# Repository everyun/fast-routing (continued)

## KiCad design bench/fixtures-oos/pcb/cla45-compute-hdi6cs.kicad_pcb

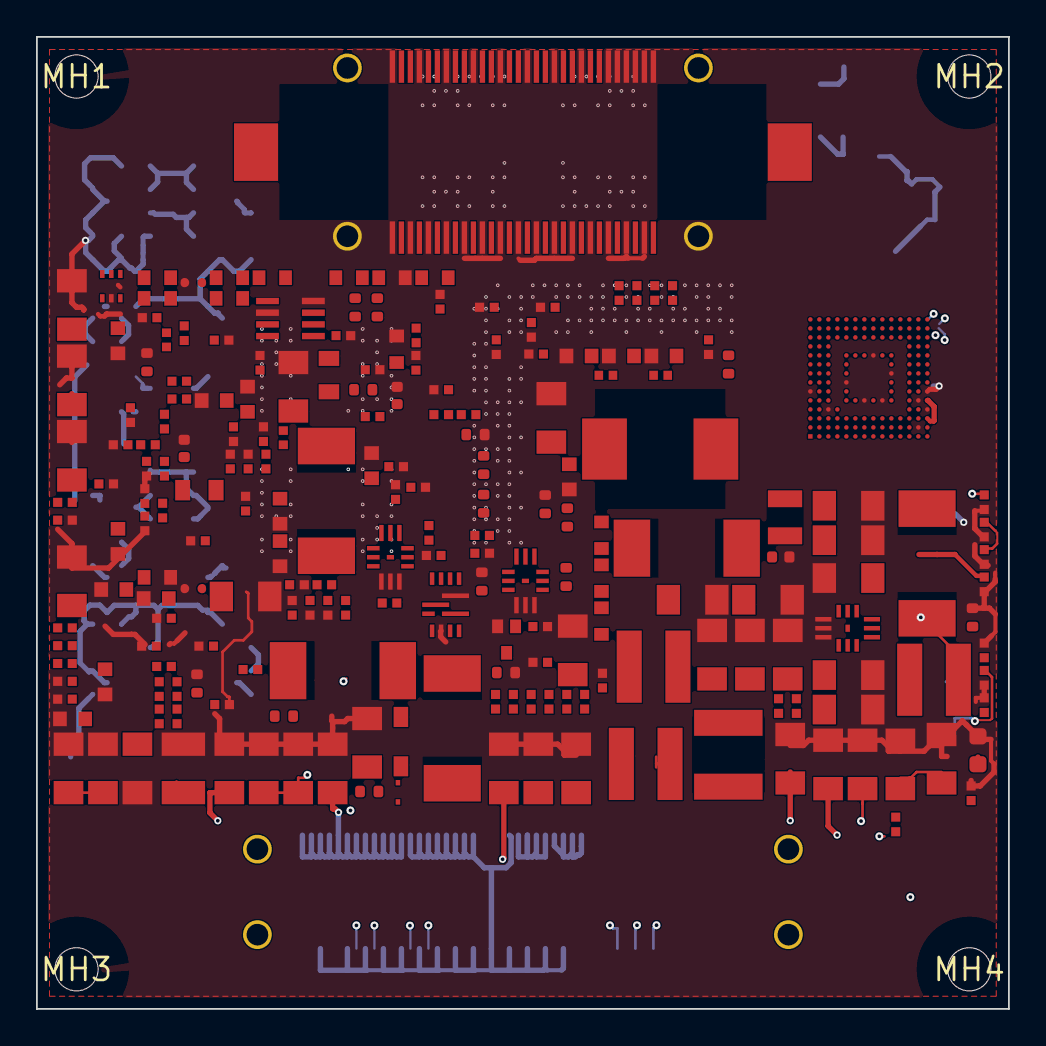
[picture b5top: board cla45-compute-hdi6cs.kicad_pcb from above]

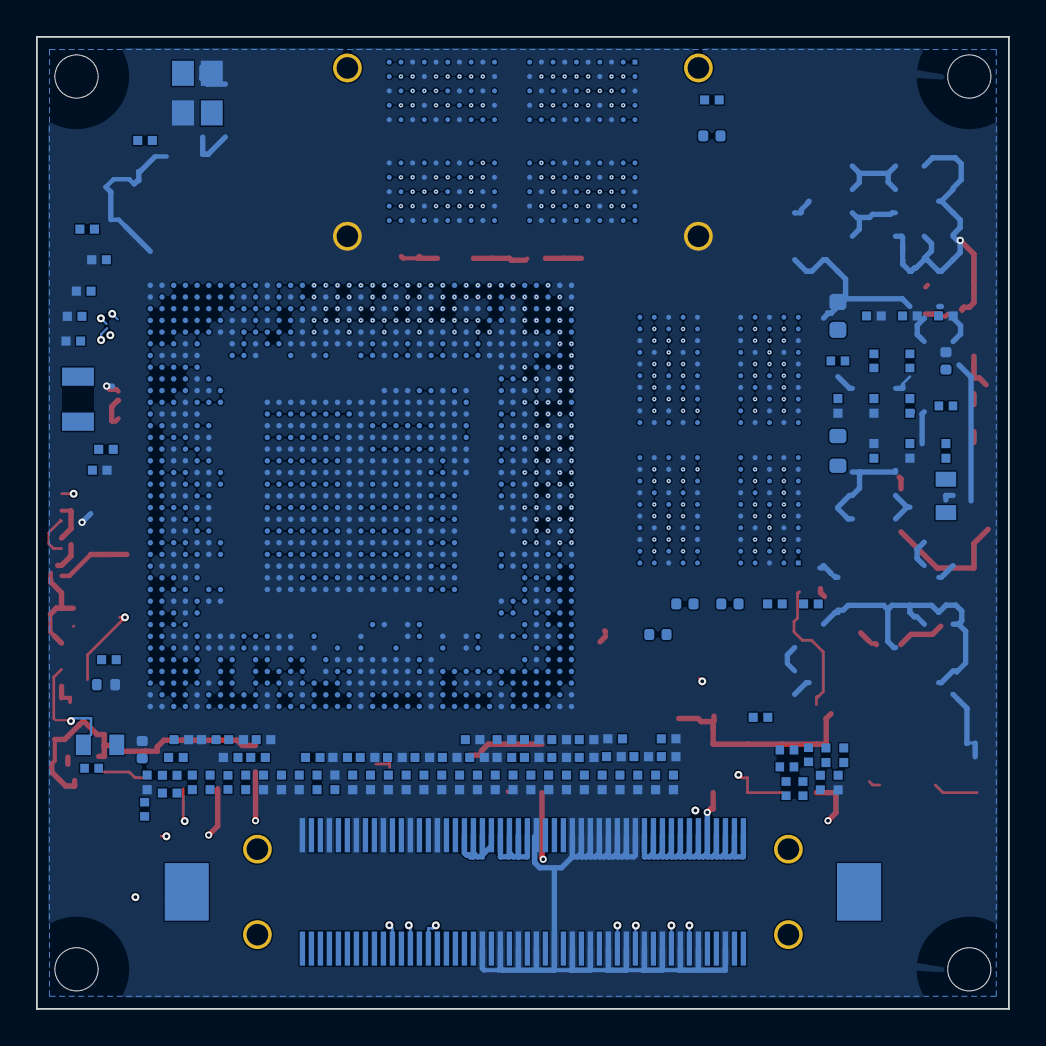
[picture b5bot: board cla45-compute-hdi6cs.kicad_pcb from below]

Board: 6 copper layers, 54.0 x 54.0 mm, 324 parts (113 on the bottom side), 363 nets.

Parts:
C4, C94, C106, C108, C113, C117, C122, C123, C176, C229, C332: SMD Ceramic Capacitor,16V,100nF,+/-10%,X7R,0402,BT
C8, C245, C319, C320, C321, C322, C323: 220nF
C9, C15, C22, C155, C156, C157, C159, C238: Chip Multilayer Ceramic Capacitor,6.3V,100uF,+/-2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
C28, C87, C88, C89, C90, C298: SMD Ceramic Capacitor,6.3V,2200nF,+/-10%,X7S,0402
C36, C99, C104, C105, C107, C116, C124, C142, C144, C145, C151, C239, C241, C247, C264, C267, C360, C425, C437, C438, C449, C451, C457, C461, C468, C478, C479, C530, C531: 100nF
C63, C400, C510, C513, C515, C517, C519, C522, C548, C550, C552, C554, C570: 10uF
C136, C545: 22pF
C137: 100pF
C140, C206, C258, C259, C260, C261, C276, C417, C418, C419, C420, C421, C422, C424, C426, C428, C429, C430, C431, C482: DMBLITE_08071747_SMD Ceramic Capacitor,10V,1000nF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
C143, C243, C257, C324, C384, C386, C387, C388, C389, C390, C391, C392, C393, C398, C403: 1uF
C149: DMBLITE_08072081_SMD Ceramic Capacitor,6.3V,4700n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
C161: DMBLITE_08070862_SMD Ceramic Capacitor,6.3V,22000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
C175, C177, C179, C180, C188, C189, C191, C192, C454, C455, C456: 22uF
C178, C181, C182, C190, C250, C252, C460: SMD Ceramic Capacitor,10V,22000nF,+/-10%,X7S,1206
C195: DMBLITE_08071624_SMD Ceramic Capacitor,6.3V,10000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
C202, C231: DMBLITE_08071990_SMD Ceramic Capacitor,6.3V,2200n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
C230, C244: SMD Ceramic Capacitor,6.3V,47000nF,+/-20%,X5R,1206
C234, C235, C499, C500: 100uF
C246: Chip Multilayer Ceramic Capacitor,50V,220pF+/-10%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
C248: Chip Multilayer Ceramic Capacitor,50V,0.1uF+/-10%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
C251: 22uF 25V X7R +/-10% 1210
C283, C329, C459, C462: DMBLITE_08070449_SMD Ceramic Capacitor,16V,10nF,+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
C325, C326, C328: 4.7uF
C334, C335: 22pF 50V C0G +/-5%
C447, C452: 18pF 50V C0G +/-5%
C800, C801, C802, C803: 1pF 25V C0G 0402 DDR CK differential shunt; C_0402_1005Metric
C810: 1uF 10V X5R 0402; C_0402_1005Metric
C811, C814: 2.2uF 10V X5R 0603; C_0603_1608Metric
C812, C813, C815, C816: 100nF 50V X7R 0402; C_0402_1005Metric
D4: DMBLITE_HBVTA002_NSR0230P2_CURRENT_MPN_LAND_HOLD
D36: DMBLITE_15010252_Silicon schottky diode,Vr=10V,If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
J_CAM: FX23L-60S-0.5SV-SEL
J_CORE: FX23L-100P-0.5SV12-SEL
L2, L6, L11: 1uH
L7: 0.4uH
L10, L12: 2.2uH
LB2, LB8, LB33, LB34, LB40, LB41, LB43, LB51, LB54, LB55: DMBLITE_10070019_EMI beads,+/-25%,1000ohm,1.25ohm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
LB21, LB50, LB53, LB56: DMBLITE_10070013_EMI beads,+/-25%,600ohm,0.65ohm,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
LB42: DMBLITE_10100616_Terminal EMI Bead,120ohm,+/-25%,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
LB52: 1000ohm@100MHz
MH1, MH2, MH3, MH4: NPTH_M2_CLEARANCE_D2.4_KEEP_OUT_D6.0
Q1: NPN 40V 600mA SOT-416/SC-75
R1, R29, R41, R43: Chip Thick Film Resistor,1/10W,27kohm,+/-1%,0603-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
R3: 3.3ohm
R4: Chip Thick Film Resistor,1/10W,12.7kohm,+/-1%,060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
R16, R42, R254, R264: 240ohm
R28, R36: 2kohm
R32: Chip Thick Film Resistor,1/16W,47kohm,+/-1%,0402
R39, R334, R339: 4.7kohm
R47: 100ohm +/-1%
R49, R50, R51: 47kohm
R60, R61, R62: 12.7kohm
R64, R71, R72, R73: 5mohm
R77: Chip Thick Film Resistor,1/16W,30kohm+/-1%,0402-P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
R78, R89: Chip Thick Film Resistor,0.0625W,10000ohm,+/-1%,0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
R79: 20kohm
R80, R246, R247, R255, R256, R424: Chip Thick Film Resistor,1/16W,1kohm-+/-1%-0402,BT
R81, R268: DMBLITE_NOT_LISTED_DNP_INTENT_AND_VALUE_HOLD
R86, R92, R118, R437: 10kohm
R87: Chip Thick Film Resistor,1/16W,12kohm,+/-1%,0402
R145: 1Mohm +/-1%
R151, R188, R189, R196, R206, R276, R297: 4.7kohm +/-1%
R153, R274, R275: Chip Thick Film Resistor,1/10W,33.2kohm+/-1%,0603
R154, R228, R250, R279, R281, R399: 0ohm
R155: DMBLITE_07110054_Chip Film Resistor,0.0625W,200oh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
R201, R231, R232, R233, R308, R414: 75kohm
R215, R467: DMBLITE_07090793_Chip Thick Film Resistor,0.0625W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
R219: DMBLITE_07090299_Chip Thick Film Resistor,0.125W,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
R226: 10kohm +/-1%
R234: Chip Thick Film Resistor,1/10W,19.6kohm,+/-1%,060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
R236, R237, R400: Chip Thick Film Resistor,0.0625W,39.2Kohm,+/-1%,0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
R238: Chip Thick Film Resistor,0.0625W,24Kohm,+/-1%,0402
R265, R271, R416, R442: 100kohm +/-1% 0402
R266, R267, R269, R270, R415, R443, R444: 100kohm
R285: 1kohm
R350, R366, R369: DMBLITE_07091282_Chip Thick Film Resistor,1/16W,1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
R385: 2mohm
R413: Chip Thick Film Resistor,0.0625W,470ohm,+/-1%,040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
R417: 511kohm
R700, R701, R703, R704, R706: 4.7kohm +/-1%; R_0402_1005Metric
R702, R714: 1kohm +/-1%; R_0402_1005Metric
R705: 10kohm +/-1%; R_0402_1005Metric
R707: 33ohm +/-1% 0402; R_0402_1005Metric
R708, R710, R712, R713: 100kohm +/-1% 0402; R_0402_1005Metric
R709, R711: 1kohm +/-1% 0402; R_0402_1005Metric
R720: 10ohm +/-1% 0603; R_0603_1608Metric
R721: 10kohm +/-1% 0402; R_0402_1005Metric
R722: 22ohm +/-1% 0402; R_0402_1005Metric
R723: 20kohm +/-1% 0402; R_0402_1005Metric
R2281: DMBLITE_07090800_Chip Thick Film Resistor,0.0625W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
U1: Hi3559AV100; Hi3559AV100_FCBGA1067_25x25_P0.65_CANDIDATE_HOLD
U2, U3: Samsung_K4F6E3S4HM-MGCJ_LCSC_C2842431_LAND_APPROV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; K4F6E3S4HM-MGCJ_FBGA200_10x15_P0.8x0.65_C2842431_CANDIDATE_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
U9, U10, U11: Switching Regulators,MP2145GD,Single Phase,2.8V,5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
U20: Switching Regulators-2.3V-5.5V-0.8-2A-2.2MHz-SOT5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
U22: Switching Regulators,MP8759GD,Single Phase,4.5V,2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
U24: Switching Regulators,Switching Regulators-Sync Bu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
U800: FORESEE_FEMDRW032G-88A19_32GB_eMMC_5.1; FEMDRW032G-88A19_FBGA153_11.5x13_P0.5_C719926_CANDIDATE_HOLD
X4: 24MHz 12pF 50ohm
X6: 32.768kHz 12.5pF +/-20ppm

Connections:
1V1_COM: C179.1, C180.1, C531.1, C545.2, L11.2, R71.1, R86.2, U11.2
1V1_SOC: C157.1, C176.1, C238.1, LB40.1, LB41.1, R16.1, R42.1, R71.2, R254.2, R264.2, U1.F9, U1.F12, U1.F15, U1.F18, U1.G9, U1.G10, U1.G12, U1.G13, U1.G15, U1.G16, U1.G18, U1.G19, U1.J6, U1.J7, U1.K7, U1.M6, U1.M7, U1.N7, U1.R6, U1.R7, U1.T7, U1.V6, U1.V7, U1.W7, U2.A4, U2.A9, U2.AA3, U2.AA5, U2.AA8, U2.AA10, U2.AB4, U2.AB9, U2.B3, U2.B5, U2.B8, U2.B10, U2.D1, U2.D5, U2.D8, U2.D12, U2.F3, U2.F5, U2.F8, U2.F10, U2.H1, U2.H5, U2.H8, U2.H12, U2.K1, U2.K3, U2.K10, U2.K12, U2.N1, U2.N3, U2.N10, U2.N12, U2.R1, U2.R5, U2.R8, U2.R12, U2.U3, U2.U5, U2.U8, U2.U10, U2.W1, U2.W5, U2.W8, U2.W12, U3.A4, U3.A9, U3.AA3, U3.AA5, U3.AA8, U3.AA10, U3.AB4, U3.AB9, U3.B3, U3.B5, U3.B8, U3.B10, U3.D1, U3.D5, U3.D8, U3.D12, U3.F3, U3.F5, U3.F8, U3.F10, U3.H1, U3.H5, U3.H8, U3.H12, U3.K1, U3.K3, U3.K10, U3.K12, U3.N1, U3.N3, U3.N10, U3.N12, U3.R1, U3.R5, U3.R8, U3.R12, U3.U3, U3.U5, U3.U8, U3.U10, U3.W1, U3.W5, U3.W8, U3.W12
1V8: C454.1, C455.1, C456.1, L10.2, R79.1, R279.1, R281.1, U20.6
1V8_PER: C36.1, C63.1, C99.1, C151.1, C234.1, C235.1, C239.1, C241.1, C264.1, C267.1, C360.1, C400.1, C425.1, C437.1, C438.1, C449.1, C451.1, C457.1, C461.1, C468.1, C479.1, C510.1, C513.1, C515.1, C517.1, C519.1, C522.1, C548.1, C550.1, C552.1, C554.1, C570.1, R28.1, R36.1, R39.1, R250.1, R281.2, R334.2, R339.2, R437.1
1V8_SOC: C814.1, C815.1, C816.1, LB2.2, LB8.1, LB21.1, LB33.2, LB34.2, LB43.1, LB50.1, LB51.1, LB52.2, LB55.2, LB56.1, R92.1, R118.1, R151.1, R188.1, R215.1, R276.1, R279.2, R467.1, R701.1, R703.1, R704.1, R706.1, R713.2, R721.2, U1.AB7, U1.AC31, U1.AG6, U1.AG31, U1.AH31, U1.AL23, U1.AL24, U1.AL27, U1.AM27, U1.AN8, U1.G24, U1.G25, U1.J31, U1.J32, U800.C6, U800.M4, U800.N4, U800.P3, U800.P5
3V3_SOC: C140.1, C149.1, C161.1, C195.1, D4.2, D36.2, R219.2, U1.F28
$6N5505: R254.1, U2.A5
$36N2755: R43.2, R234.1
$36N2756: C90.1, R43.1, R256.2
$36N2757: L2.1, U24.3
$36N2758: R50.1, U24.7
$36N2768: R50.2, R62.2, R234.2, R238.1
$36N3231: C89.1, R41.1, R255.2
$36N3232: R41.2, R237.1
$36N3233: C124.1, R270.2, R271.1, U10.6
$36N3234: R269.2, U10.7
$36N3235: C137.1, U10.4
$36N3236: R51.2, R61.2, R237.2, R275.1
$36N3237: R51.1, U10.3
$36N3238: L7.1, U10.1, U10.9
$36N3239: C144.1, R232.2, U10.5
$36N3756: C145.1, R233.2, U24.8
$37N2984: R29.2, R236.1
$37N2985: C87.1, R29.1, R246.2
$37N2987: L6.1, U9.1, U9.9
$37N2988: R49.1, U9.3
$37N2989: R49.2, R60.2, R236.2, R274.1
$37N2990: C136.1, U9.4
$37N2991: R267.2, U9.7
$37N2992: C105.1, R265.1, R266.2, U9.6
$37N3001: R228.1, U20.1
$37N3002: R78.1, R81.2, R228.2, R2281.2
$37N3003: C243.1, Q1.3, R308.2, U20.5
$37N3004: L10.1, U20.4
$37N3837: C142.1, R231.2, U9.5
$37N3940: Q1.1, R89.1
$37N3991: C28.1, R77.1, R80.2
$37N4018: R77.2, R81.1
$37N4041: R79.2, R2281.1
$38N1625: C143.1, R201.2, U11.5
$38N1626: R86.1, R87.2, R154.1, R268.2
$38N1627: R154.2, U11.3
$38N1638: C88.1, R32.1, R247.2
$38N1640: R32.2, R268.1
$38N2600: L11.1, U11.1, U11.9
$38N2603: C545.1, U11.4
$38N2608: C530.1, R442.1, R443.2, U11.6
$38N2609: R444.2, U11.7
$41N4060: R264.1, U3.A5
$54N37: R1.2, R400.1
$54N38: C298.1, R1.1, R424.2
$54N2464: R399.1, U22.11
$54N2465: R4.2, R153.1, R399.2, R400.2, R413.2
$54N2466: C257.1, R415.1, U22.9
$54N2467: C246.1, R413.1, R417.2
$54N2468: C245.1, R3.2
$54N2469: R3.1, U22.8
$54N2470: C245.2, L12.1, R417.1, U22.7
$54N2471: C104.1, R414.2, U22.12
$54N2472: R415.2, R416.1, U22.6
+1V8_AUX: J_CORE.25, J_CORE.26, J_CORE.27, J_CORE.28
+3V3_AUX: C811.1, C812.1, C813.1, J_CORE.29, J_CORE.30, J_CORE.31, J_CORE.32, R219.1, U800.E6, U800.F5, U800.J10, U800.K9
+3V3_SENSOR: J_CAM.P1, J_CAM.P2
+5V_PROTECTED: C106.1, C113.1, C117.1, C123.1, C178.1, C181.1, C182.1, C190.1, C248.1, C250.1, C252.1, C332.1, C460.1, J_CORE.1, J_CORE.2, J_CORE.3, J_CORE.4, J_CORE.5, J_CORE.6, J_CORE.7, J_CORE.8, J_CORE.9, J_CORE.10, J_CORE.11, J_CORE.12, R89.2, R201.1, R231.1, R232.1, R233.1, R266.1, R267.1, R269.1, R270.1, R308.1, R414.1, R443.1, R444.1, U9.8, U9.13, U10.8, U10.13, U11.8, U11.13, U20.3, U22.1, U24.2
ACC_ON: J_CORE.90, R709.1
ACC_ON_SENSE: R709.2, R710.1, U1.B34
AUX_I2C_SCL: J_CAM.46, U1.G35
AUX_I2C_SDA: J_CAM.48, U1.G34
AVDD08_HDMITX: C329.1, C417.1, LB42.2, U1.P30
AVDD08_PLL: C420.1, LB54.1, U1.T18
AVDD08_UFSCOMB: C430.1, LB53.1, U1.AM11
AVDD18_AC: C231.1, LB56.2, U1.AA32
AVDD18_DDR0_PLL: C260.1, LB34.1, U1.K13, U1.K14
AVDD18_DDR1_PLL: C259.1, LB33.1, U1.N10, U1.P10
AVDD18_HDMITX: C283.1, C418.1, LB43.2, U1.W32
AVDD18_LSADC0: C258.1, LB2.1, U1.AK7
AVDD18_MIPITX: C206.1, LB21.2, U1.M32
AVDD18_PLL: C421.1, LB55.1, U1.V18
AVDD18_SHUB_LSADC1: C482.1, LB8.2, U1.AJ7
AVDD18_UFSCOMB: C431.1, LB50.2, U1.AL10, U1.AM9
AVDD1218_UFSCOMB: C429.1, LB52.1, U1.AL11
AVDDDRV_HDMITX: C419.1, C459.1, D4.1, U1.V30
AVDDPLL_HDMITX: C428.1, C462.1, LB51.2, U1.P31
AVDD_BAT_RTC: D36.1, U1.AJ5
BOOT_SEL0: R196.1, U1.AT35
BOOT_SEL1: R188.2, R714.1, U1.AN33
BOOT_SEL2: R206.1, U1.AN29
BOOT_SEL3: R189.1, U1.AR29
BOOT_SEL4: R297.1, U1.AU33
BT_DEV_WAKE_FROM_SOC: J_CORE.21, U1.C29
BT_HOST_WAKE_TO_SOC: J_CORE.22, U1.A34
BT_REG_ON_FROM_SOC: J_CORE.85, U1.F34
BT_UART_CTS_N_FROM_SOC: J_CORE.83, U1.AG33
BT_UART_RTS_N_TO_SOC: J_CORE.84, U1.AG34
BT_UART_RX_TO_SOC: J_CORE.82, U1.AE34
BT_UART_TX_FROM_SOC: J_CORE.81, U1.AE33
CAM_PRESENT: J_CAM.56, R713.1, U1.C34
CAM_PWR_EN: J_CAM.54, R707.2
CAM_PWR_EN_SRC: R707.1, R708.1, U1.E35
DDR0_CA0_A: U1.B6, U2.H2
DDR0_CA0_B: U1.E5, U2.R2
DDR0_CA1_A: U1.A7, U2.J2
DDR0_CA1_B: U1.D5, U2.P2
DDR0_CA2_A: U1.A10, U2.H9
DDR0_CA2_B: U1.E8, U2.R9
DDR0_CA3_A: U1.A6, U2.H10
DDR0_CA3_B: U1.D10, U2.R10
DDR0_CA4_A: U1.B9, U2.H11
DDR0_CA4_B: U1.A9, U2.R11
DDR0_CA5_A: U1.A8, U2.J11
DDR0_CA5_B: U1.B10, U2.P11
DDR0_CKE0_A: U1.B11, U2.J4
DDR0_CKE0_B: U1.B5, U2.P4
DDR0_CK_C_A: C800.2, U1.E11, U2.J9
DDR0_CK_C_B: C801.2, U1.D9, U2.P9
DDR0_CK_T_A: C800.1, U1.D11, U2.J8
DDR0_CK_T_B: C801.1, U1.E9, U2.P8
DDR0_CS0_A: U1.C11, U2.H4
DDR0_CS0_B: U1.B4, U2.R4
DDR0_DMI0_A: U1.A20, U2.C3
DDR0_DMI0_B: U1.C16, U2.Y3
DDR0_DMI1_A: U1.D18, U2.C10
DDR0_DMI1_B: U1.A13, U2.Y10
DDR0_DQ0_A: U1.D19, U2.B2
DDR0_DQ0_B: U1.B17, U2.AA2
DDR0_DQ1_A: U1.B23, U2.C2
DDR0_DQ1_B: U1.A17, U2.Y2
DDR0_DQ2_A: U1.C21, U2.E2
DDR0_DQ2_B: U1.A16, U2.V2
DDR0_DQ3_A: U1.D22, U2.F2
DDR0_DQ3_B: U1.C15, U2.U2
DDR0_DQ4_A: U1.B18, U2.F4
DDR0_DQ4_B: U1.D16, U2.U4
DDR0_DQ5_A: U1.A22, U2.E4
DDR0_DQ5_B: U1.D15, U2.V4
DDR0_DQ6_A: U1.A18, U2.C4
DDR0_DQ6_B: U1.C13, U2.Y4
DDR0_DQ7_A: U1.A23, U2.B4
DDR0_DQ7_B: U1.D12, U2.AA4
DDR0_DQ8_A: U1.C18, U2.B11
DDR0_DQ8_B: U1.D13, U2.AA11
DDR0_DQ9_A: U1.B20, U2.C11
DDR0_DQ9_B: U1.C12, U2.Y11
DDR0_DQ10_A: U1.A21, U2.E11
DDR0_DQ10_B: U1.A15, U2.V11
DDR0_DQ11_A: U1.C19, U2.F11
DDR0_DQ11_B: U1.B14, U2.U11
DDR0_DQ12_A: U1.A19, U2.F9
DDR0_DQ12_B: U1.A14, U2.U9
DDR0_DQ13_A: U1.D21, U2.E9
DDR0_DQ13_B: U1.B15, U2.V9
DDR0_DQ14_A: U1.B21, U2.C9
DDR0_DQ14_B: U1.A12, U2.Y9
DDR0_DQ15_A: U1.C22, U2.B9
DDR0_DQ15_B: U1.B12, U2.AA9
DDR0_DQS0_C_A: U1.D20, U2.E3
DDR0_DQS0_C_B: U1.E14, U2.V3
DDR0_DQS0_T_A: U1.E20, U2.D3
DDR0_DQS0_T_B: U1.D14, U2.W3
DDR0_DQS1_C_A: U1.E23, U2.E10
DDR0_DQS1_C_B: U1.E17, U2.V10
DDR0_DQS1_T_A: U1.D23, U2.D10
DDR0_DQS1_T_B: U1.D17, U2.W10
DDR0_ODT_CA_A: U1.B8, U2.G2
DDR0_ODT_CA_B: U1.A3, U2.T2
DDR0_RESET_N: U1.D4, U2.T11
DDR0_ZQ: R42.2, U1.B3
DDR1_CA0_A: U1.F2, U3.H2
DDR1_CA0_B: U1.E3, U3.R2
DDR1_CA1_A: U1.G1, U3.J2
DDR1_CA1_B: U1.E4, U3.P2
DDR1_CA2_A: U1.K1, U3.H9
DDR1_CA2_B: U1.K4, U3.R9
DDR1_CA3_A: U1.H5, U3.H10
DDR1_CA3_B: U1.J1, U3.R10
DDR1_CA4_A: U1.F1, U3.H11
DDR1_CA4_B: U1.J2, U3.R11
DDR1_CA5_A: U1.K2, U3.J11
DDR1_CA5_B: U1.H1, U3.P11
DDR1_CKE0_A: U1.L3, U3.J4
DDR1_CKE0_B: U1.E2, U3.P4
DDR1_CK_C_A: C802.2, U1.L5, U3.J9
DDR1_CK_C_B: C803.2, U1.J4, U3.P9
DDR1_CK_T_A: C802.1, U1.L4, U3.J8
DDR1_CK_T_B: C803.1, U1.J5, U3.P8
DDR1_CS0_A: U1.L2, U3.H4
DDR1_CS0_B: U1.D2, U3.R4
DDR1_DMI0_A: U1.T4, U3.C3
DDR1_DMI0_B: U1.Y1, U3.Y3
DDR1_DMI1_A: U1.N1, U3.C10
DDR1_DMI1_B: U1.V1, U3.Y10
DDR1_DQ0_A: U1.U2, U3.B2
DDR1_DQ0_B: U1.AC1, U3.AA2
DDR1_DQ1_A: U1.T1, U3.C2
DDR1_DQ1_B: U1.W4, U3.Y2
DDR1_DQ2_A: U1.R3, U3.E2
DDR1_DQ2_B: U1.AA4, U3.V2
DDR1_DQ3_A: U1.U1, U3.F2
DDR1_DQ3_B: U1.W1, U3.U2
DDR1_DQ4_A: U1.T3, U3.F4
DDR1_DQ4_B: U1.V2, U3.U4
DDR1_DQ5_A: U1.N3, U3.E4
DDR1_DQ5_B: U1.AB1, U3.V4
DDR1_DQ6_A: U1.R4, U3.C4
DDR1_DQ6_B: U1.AA3, U3.Y4
DDR1_DQ7_A: U1.M4, U3.B4
DDR1_DQ7_B: U1.AC2, U3.AA4
DDR1_DQ8_A: U1.N4, U3.B11
DDR1_DQ8_B: U1.V3, U3.AA11
DDR1_DQ9_A: U1.M3, U3.C11
DDR1_DQ9_B: U1.AA2, U3.Y11
DDR1_DQ10_A: U1.P2, U3.E11
DDR1_DQ10_B: U1.AA1, U3.V11
DDR1_DQ11_A: U1.R2, U3.F11
DDR1_DQ11_B: U1.W3, U3.U11
DDR1_DQ12_A: U1.R1, U3.F9
DDR1_DQ12_B: U1.AB4, U3.U9
DDR1_DQ13_A: U1.P1, U3.E9
DDR1_DQ13_B: U1.V4, U3.V9
DDR1_DQ14_A: U1.M1, U3.C9
DDR1_DQ14_B: U1.Y2, U3.Y9
DDR1_DQ15_A: U1.M2, U3.B9
DDR1_DQ15_B: U1.AB3, U3.AA9
DDR1_DQS0_C_A: U1.U5, U3.E3
DDR1_DQS0_C_B: U1.AC5, U3.V3
DDR1_DQS0_T_A: U1.U4, U3.D3
DDR1_DQS0_T_B: U1.AC4, U3.W3
DDR1_DQS1_C_A: U1.P5, U3.E10
DDR1_DQS1_C_B: U1.Y5, U3.V10
DDR1_DQS1_T_A: U1.P4, U3.D10
DDR1_DQS1_T_B: U1.Y4, U3.W10
DDR1_ODT_CA_A: U1.H2, U3.G2
DDR1_ODT_CA_B: U1.C1, U3.T2
DDR1_RESET_N: U1.C3, U3.T11
DDR1_ZQ: R16.2, U1.B2
DVDD: C108.1, C155.1, C156.1, LB42.1, LB53.2, LB54.2, R64.2, U1.AJ31, U1.AJ32, U1.AL17, U1.AL18, U1.M16, U1.M17, U1.N13, U1.N15, U1.N17, U1.P13, U1.P15, U1.R13, U1.R15, U1.T13, U1.T15, U1.U13, U1.U15, U1.V13, U1.V15
DVDD18_LDO_DECAP_1: C424.1, U1.G29
DVDD18_LDO_DECAP_2: C422.1, U1.F31
DVDD18_LDO_DECAP_3: C426.1, U1.F29
DVDD_COM: C107.1, C136.2, C175.1, C177.1, L6.2, R60.1, R64.1, U9.2
DVDD_CPU: C9.1, C122.1, C159.1, R73.2, U1.L19, U1.L21, U1.L23, U1.L25, U1.L27, U1.M19, U1.M21, U1.M23, U1.M25, U1.M27, U1.N19, U1.N21, U1.N23, U1.N25, U1.N27
DVDD_CPU_COM: C191.1, C192.1, L2.2, R62.1, R73.1, U24.5
DVDD_GPU: C4.1, C15.1, C22.1, R72.2, U1.R20, U1.R22, U1.R24, U1.R26, U1.T20, U1.T22, U1.T24, U1.T26, U1.U20, U1.U22, U1.U24, U1.U26, U1.V20, U1.V22, U1.V24, U1.V26, U1.W20, U1.W22, U1.W24, U1.W26
DVDD_GPU_COM: C116.1, C137.2, C188.1, C189.1, L7.2, R61.1, R72.1, U10.2
DVDD_MEDIA: C8.1, C247.1, C319.1, C320.1, C321.1, C322.1, C323.1, C324.1, C325.1, C326.1, C328.1, C384.1, C386.1, C387.1, C388.1, C389.1, C390.1, C391.1, C392.1, C393.1, C398.1, C403.1, C478.1, C499.1, C500.1, R385.2, U1.AA12, U1.AA14, U1.AA16, U1.AA18, U1.AA20, U1.AA22, U1.AA24, U1.AA26, U1.AB12, U1.AB14, U1.AB16, U1.AB18, U1.AB20, U1.AB22, U1.AB24, U1.AB26, U1.AC12, U1.AC14, U1.AC16, U1.AC18, U1.AC20, U1.AC22, U1.AC24, U1.AC26, U1.AD12, U1.AD14, U1.AD16, U1.AD18, U1.AD20, U1.AD22, U1.AD24, U1.AD26, U1.AE12, U1.AE14, U1.AE16, U1.AE18, U1.AE20, U1.AE22, U1.AE24, U1.AF12, U1.AF14, U1.AF16, U1.AF18, U1.AF20, U1.AF22, U1.AF24, U1.AG12, U1.AG14, U1.AG16, U1.AG18, U1.AG20, U1.AG22, U1.AG24, U1.Y12, U22.5
DVDD_MEDIA_COM: C94.1, C229.1, C230.1, C244.1, C246.2, C251.1, L12.2, R4.1, R385.1
DVDD_SENHUB_LDO_DECAP: C202.1, U1.AE7
EMMC_CALIO: R155.1, U1.AR8
EMMC_CLK: R720.1, U1.AP8
EMMC_CLK_DEV: R720.2, U800.M6
EMMC_CMD: R721.1, U1.AR9, U800.M5
EMMC_DATA0: U1.AU9, U800.A3
EMMC_DATA1: U1.AU10, U800.A4
EMMC_DATA2: U1.AT8, U800.A5
EMMC_DATA3: U1.AT9, U800.B2
EMMC_DATA4: U1.AT10, U800.B3
EMMC_DATA5: U1.AU8, U800.B4
EMMC_DATA6: U1.AT11, U800.B5
EMMC_DATA7: U1.AU11, U800.B6
EMMC_DS: R722.2, R723.1, U1.AP9
EMMC_DS_DEV: R722.1, U800.H5
EMMC_RST_N: U1.AR10, U800.K5
EMMC_VDDI: C810.1, U800.C2
EPHY0_RSTN: J_CORE.54, U1.E25
EPHY_CLK: J_CORE.55, U1.B26
GND: C4.2, C8.2, C9.2, C15.2, C22.2, C28.2, C36.2, C63.2, C87.2, C88.2, C89.2, C90.2, C94.2, C99.2, C104.2, C105.2, C106.2, C107.2, C108.2, C113.2, C116.2, C117.2, C122.2, C123.2, C124.2, C140.2, C142.2, C143.2, C144.2, C145.2, C149.2, C151.2, C155.2, C156.2, C157.2, C159.2, C161.2, C175.2, C176.2, C177.2, C178.2, C179.2, C180.2, C181.2, C182.2, C188.2, C189.2, C190.2, C191.2, C192.2, C195.2, C202.2, C206.2, C229.2, C230.2, C231.2, C234.2, C235.2, C238.2, C239.2, C241.2, C243.2, C244.2, C247.2, C248.2, C250.2, C251.2, C252.2, C257.2, C258.2, C259.2, C260.2, C261.2, C264.2, C267.2, C276.2, C283.2, C298.2, C319.2, C320.2, C321.2, C322.2, C323.2, C324.2, C325.2, C326.2, C328.2, C329.2, C332.2, C334.2, C335.2, C360.2, C384.2, C386.2, C387.2, C388.2, C389.2, C390.2, C391.2, C392.2, C393.2, C398.2, C400.2, C403.2, C417.2, C418.2, C419.2, C420.2, C421.2, C422.2, C424.2, C425.2, C426.2, C428.2, C429.2, C430.2, C431.2, C437.2, C438.2, C447.2, C449.2, C451.2, C452.2, C454.2, C455.2, C456.2, C457.2, C459.2, C460.2, C461.2, C462.2, C468.2, C478.2, C479.2, C482.2, C499.2, C500.2, C510.2, C513.2, C515.2, C517.2, C519.2, C522.2, C530.2, C531.2, C548.2, C550.2, C552.2, C554.2, C570.2, C810.2, C811.2, C812.2, C813.2, C814.2, C815.2, C816.2, J_CAM.1, J_CAM.4, J_CAM.7, J_CAM.10, J_CAM.13, J_CAM.16, J_CAM.19, J_CAM.22, J_CAM.25, J_CAM.26, J_CAM.27, J_CAM.28, J_CAM.29, J_CAM.30, J_CAM.31, J_CAM.33, J_CAM.35, J_CAM.37, J_CAM.39, J_CAM.41, J_CAM.43, J_CAM.45, J_CAM.47, J_CAM.49, J_CAM.51, J_CAM.53, J_CAM.55, J_CAM.57, J_CAM.59, J_CAM.P3, J_CAM.P4, J_CORE.13, J_CORE.14, J_CORE.15, J_CORE.16, J_CORE.17, J_CORE.18, J_CORE.19, J_CORE.20, J_CORE.24, J_CORE.35, J_CORE.38, J_CORE.41, J_CORE.44, J_CORE.47, J_CORE.50, J_CORE.53, J_CORE.56, J_CORE.58, J_CORE.60, J_CORE.62, J_CORE.64, J_CORE.66, J_CORE.68, J_CORE.70, J_CORE.72, J_CORE.74, J_CORE.76, J_CORE.78, J_CORE.80, Q1.2, R78.2, R87.1, R153.2, R155.2, R189.2, R196.2, R206.2, R226.2, R238.2, R265.2, R271.2, R274.2, R275.2, R285.2, R297.2, R350.2, R366.2, R369.2, R416.2, R442.2, R700.2, R702.2, R705.2, R708.2, R710.2, R712.2, R714.2, R723.2, U1.A1, U1.A2, U1.A24, U1.A36, U1.A37, U1.AA5, U1.AA6, U1.AA11, U1.AA13, U1.AA15, U1.AA17, U1.AA19, U1.AA21, U1.AA23, U1.AA25, U1.AA27, U1.AA33, U1.AB2, U1.AB5, U1.AB6, U1.AB11, U1.AB13, U1.AB15, U1.AB17, U1.AB19, U1.AB21, U1.AB23, U1.AB25, U1.AB27, U1.AB34, U1.AC3, U1.AC6, U1.AC7, U1.AC11, U1.AC13, U1.AC15, U1.AC17, U1.AC19, U1.AC21, U1.AC23, U1.AC25, U1.AC27, U1.AC32, U1.AD4, U1.AD5, U1.AD6, U1.AD11, U1.AD13, U1.AD15, U1.AD17, U1.AD19, U1.AD21, U1.AD23, U1.AD25, U1.AD27, U1.AD36, U1.AE2, U1.AE6, U1.AE11, U1.AE13, U1.AE15, U1.AE17, U1.AE19, U1.AE21, U1.AE23, U1.AE25, U1.AE26, U1.AE27, U1.AE31, U1.AE32, U1.AE35, U1.AF11, U1.AF13, U1.AF15, U1.AF17, U1.AF19, U1.AF21, U1.AF23, U1.AF25, U1.AF26, U1.AF27, U1.AF31, U1.AF32, U1.AG1, U1.AG2, U1.AG4, U1.AG11, U1.AG13, U1.AG15, U1.AG17, U1.AG19, U1.AG21, U1.AG23, U1.AG25, U1.AG26, U1.AG27, U1.AG32, U1.AG36, U1.AG37, U1.AH6, U1.AH7, U1.AH32, U1.AJ2, U1.AJ4, U1.AK4, U1.AK5, U1.AK6, U1.AK31, U1.AK32, U1.AL5, U1.AL28, U1.AL31, U1.AL32, U1.AM10, U1.AM14, U1.AM15, U1.AM17, U1.AM18, U1.AM20, U1.AM21, U1.AM23, U1.AM24, U1.AM28, U1.AM31, U1.AM32, U1.AM35, U1.AN7, U1.AN9, U1.AN10, U1.AN12, U1.AN14, U1.AN17, U1.AN20, U1.AN23, U1.AN25, U1.AN36, U1.AN37, U1.AP6, U1.AP7, U1.AP11, U1.AP12, U1.AP13, U1.AP16, U1.AP19, U1.AP22, U1.AP25, U1.AP26, U1.AP28, U1.AP29, U1.AP31, U1.AP32, U1.AR7, U1.AR12, U1.AR13, U1.AR15, U1.AR16, U1.AR18, U1.AR19, U1.AR21, U1.AR22, U1.AR24, U1.AR25, U1.AR28, U1.AR31, U1.AT1, U1.AT7, U1.AT12, U1.AT25, U1.AT37, U1.AU1, U1.AU2, U1.AU36, U1.AU37, U1.B1, U1.B13, U1.B16, U1.B19, U1.B22, U1.B37, U1.C6, U1.C9, U1.C10, U1.C14, U1.C17, U1.C20, U1.C23, U1.C25, U1.C28, U1.C31, U1.D6, U1.D24, U1.D25, U1.D27, U1.D28, U1.D30, U1.D31, U1.D33, U1.E6, U1.E7, U1.E10, U1.E12, U1.E13, U1.E15, U1.E16, U1.E18, U1.E19, U1.E21, U1.E22, U1.E24, U1.F3, U1.F4, U1.F5, U1.F6, U1.F7, U1.F8, U1.F10, U1.F11, U1.F13, U1.F14, U1.F16, U1.F17, U1.F19, U1.F20, U1.F21, U1.F22, U1.F24, U1.F25, U1.G5, U1.G6, U1.G7, U1.G8, U1.G11, U1.G14, U1.G17, U1.G20, U1.G28, U1.G31, U1.G36, U1.G37, U1.H6, U1.H7, U1.H35, U1.J3, U1.J35, U1.K3, U1.K5, U1.K6, U1.K10, U1.K12, U1.K15, U1.K16, U1.K17, U1.K31, U1.K32, U1.K35, U1.L6, U1.L7, U1.L11, U1.L12, U1.L13, U1.L14, U1.L15, U1.L16, U1.L17, U1.L18, U1.L20, U1.L22, U1.L24, U1.L26, U1.M5, U1.M10, U1.M11, U1.M12, U1.M13, U1.M14, U1.M15, U1.M18, U1.M20, U1.M22, U1.M24, U1.M26, U1.M31, U1.N2, U1.N5, U1.N6, U1.N11, U1.N12, U1.N14, U1.N16, U1.N18, U1.N20, U1.N22, U1.N24, U1.N26, U1.N33, U1.N34, U1.N35, U1.N36, U1.N37, U1.P3, U1.P6, U1.P7, U1.P11, U1.P12, U1.P14, U1.P16, U1.P17, U1.P18, U1.P19, U1.P20, U1.P21, U1.P22, U1.P23, U1.P24, U1.P25, U1.P26, U1.P27, U1.P35, U1.R5, U1.R10, U1.R11, U1.R12, U1.R14, U1.R16, U1.R17, U1.R18, U1.R19, U1.R21, U1.R23, U1.R25, U1.R27, U1.R30, U1.R31, U1.R33, U1.R34, U1.R35, U1.T2, U1.T5, U1.T6, U1.T10, U1.T11, U1.T12, U1.T14, U1.T16, U1.T17, U1.T19, U1.T21, U1.T23, U1.T25, U1.T27, U1.T33, U1.T34, U1.T35, U1.U3, U1.U6, U1.U7, U1.U10, U1.U11, U1.U12, U1.U14, U1.U16, U1.U17, U1.U18, U1.U19, U1.U21, U1.U23, U1.U25, U1.U27, U1.U30, U1.U33, U1.U34, U1.U35, U1.V5, U1.V11, U1.V12, U1.V14, U1.V16, U1.V17, U1.V19, U1.V21, U1.V23, U1.V25, U1.V27, U1.V33, U1.V34, U1.V35, U1.W2, U1.W5, U1.W6, U1.W11, U1.W12, U1.W13, U1.W14, U1.W15, U1.W16, U1.W17, U1.W18, U1.W19, U1.W21, U1.W23, U1.W25, U1.W27, U1.W31, U1.W33, U1.W34, U1.W35, U1.W36, U1.W37, U1.Y3, U1.Y6, U1.Y11, U1.Y13, U1.Y14, U1.Y15, U1.Y16, U1.Y17, U1.Y18, U1.Y19, U1.Y20, U1.Y21, U1.Y22, U1.Y23, U1.Y24, U1.Y25, U1.Y26, U1.Y27, U1.Y33, U1.Y35, U2.A3, U2.A10, U2.AB3, U2.AB5, U2.AB8, U2.AB10, U2.C1, U2.C5, U2.C8, U2.C12, U2.D2, U2.D4, U2.D9, U2.D11, U2.E1, U2.E5, U2.E8, U2.E12, U2.G1, U2.G3, U2.G5, U2.G8, U2.G10, U2.G12, U2.J1, U2.J3, U2.J10, U2.J12, U2.K2, U2.K4, U2.K9, U2.K11, U2.N2, U2.N4, U2.N9, U2.N11, U2.P1, U2.P3, U2.P10, U2.P12, U2.T1, U2.T3, U2.T5, U2.T8, U2.T10, U2.T12, U2.V1, U2.V5, U2.V8, U2.V12, U2.W2, U2.W4, U2.W9, U2.W11, U2.Y1, U2.Y5, U2.Y8, U2.Y12, U3.A3, U3.A10, U3.AB3, U3.AB5, U3.AB8, U3.AB10, U3.C1, U3.C5, U3.C8, U3.C12, U3.D2, U3.D4, U3.D9, U3.D11, U3.E1, U3.E5, U3.E8, U3.E12, U3.G1, U3.G3, U3.G5, U3.G8, U3.G10, U3.G12, U3.J1, U3.J3, U3.J10, U3.J12, U3.K2, U3.K4, U3.K9, U3.K11, U3.N2, U3.N4, U3.N9, U3.N11, U3.P1, U3.P3, U3.P10, U3.P12, U3.T1, U3.T3, U3.T5, U3.T8, U3.T10, U3.T12, U3.V1, U3.V5, U3.V8, U3.V12, U3.W2, U3.W4, U3.W9, U3.W11, U3.Y1, U3.Y5, U3.Y8, U3.Y12, U9.10, U9.11, U9.12, U10.10, U10.11, U10.12, U11.10, U11.11, U11.12, U20.2, U22.2, U22.10, U24.4, U24.6, U800.A6, U800.C4, U800.E7, U800.G5, U800.H10, U800.J5, U800.K8, U800.N2, U800.N5, U800.P4, U800.P6, X4.2, X4.4
GNSS_1PPS_TO_SOC: J_CORE.97, U1.B35
GNSS_TX_TO_SOC_UART2_RX: J_CORE.95, U1.AF34
I2C11_SCL_3V3_OD: J_CORE.93, U1.F37
I2C11_SDA_3V3_OD: J_CORE.94, U1.F36
IMU_INT1: J_CAM.50, U1.B33
INCK_72MHZ: J_CAM.32, U1.AU27
JTAG_EN: R151.2, U1.AD37
JTAG_TCK: R702.1, U1.AC37
JTAG_TDI: R703.2, U1.AB37
JTAG_TDO: R706.2, U1.AD35
JTAG_TMS: R704.2, U1.AC36
JTAG_TRSTN: R705.1, U1.AB36
MDCK: J_CORE.52, U1.B25
MDIO: J_CORE.51, U1.C26
POR_SEL: R276.2, R285.1, U1.AU12
PWR_FAIL: J_CORE.91, R711.1
PWR_FAIL_SENSE: R711.2, R712.1, U1.E34
RESERVED_AUX_GPIO_1V8: J_CORE.98, U1.A35
RGMII0_RXCK: J_CORE.42, U1.A25
RGMII0_RXD0: J_CORE.43, U1.C27
RGMII0_RXD1: J_CORE.45, U1.E27
RGMII0_RXD2: J_CORE.46, U1.E26
RGMII0_RXD3: J_CORE.48, U1.D26
RGMII0_RXDV: J_CORE.49, U1.B24
RGMII0_TXCKOUT: J_CORE.33, U1.B28
RGMII0_TXD0: J_CORE.34, U1.A28
RGMII0_TXD1: J_CORE.36, U1.B27
RGMII0_TXD2: J_CORE.37, U1.A27
RGMII0_TXD3: J_CORE.39, U1.A26
RGMII0_TXEN: J_CORE.40, U1.C24
RTC_XIN: C334.1, U1.AH2, X6.1
RTC_XOUT: C335.1, U1.AH1, X6.2
SCK: J_CAM.34, U1.AT26
SDI: J_CAM.36, U1.AN26
SENSOR_HS2/PCIE_USB3_MODE1: R350.1, U1.AU31
SENSOR_HS3/PCIE_DEEMPH_SEL: R369.1, U1.AT33
SENSOR_VS1/PCIE_USB3_MODE0: R215.2, U1.AU28
SENSOR_VS2/PCIE_REFCLK_SEL: R366.1, U1.AT30
SFC_CLK: J_CORE.59, U1.AU5
SFC_CS0N: J_CORE.57, R339.1, U1.AT5
SFC_EMMC_BOOT_MODE: R92.2, R701.2, U1.AT28
SFC_HOLD_IO3: J_CORE.67, R334.1, U1.AT6
SFC_MISO_IO1: J_CORE.63, U1.AU6
SFC_MOSI_IO0: J_CORE.61, U1.AR6
SFC_WP_IO2: J_CORE.65, U1.AU7
SHUB_PWM_OUT0: R247.1, U1.AD1
SHUB_PWM_OUT7: R80.1, U1.AF3
SLVS_D0_N: J_CAM.3, U1.AU23
SLVS_D0_P: J_CAM.2, U1.AT23
SLVS_D1_N: J_CAM.6, U1.AU24
SLVS_D1_P: J_CAM.5, U1.AT24
SLVS_D2_N: J_CAM.9, U1.AP23
SLVS_D2_P: J_CAM.8, U1.AR23
SLVS_D3_N: J_CAM.12, U1.AN24
SLVS_D3_P: J_CAM.11, U1.AP24
SLVS_D4_N: J_CAM.15, U1.AP21
SLVS_D4_P: J_CAM.14, U1.AN21
SLVS_D5_N: J_CAM.18, U1.AT20
SLVS_D5_P: J_CAM.17, U1.AU20
SLVS_D6_N: J_CAM.21, U1.AR20
SLVS_D6_P: J_CAM.20, U1.AP20
SLVS_D7_N: J_CAM.24, U1.AT21
SLVS_D7_P: J_CAM.23, U1.AU21
SOC_UART2_TX_TO_GNSS_RX: J_CORE.96, U1.AF35
SPI4_CSN0: R39.2, U1.J34
SVB_PWM0: R246.1, U1.Y36
SVB_PWM1: R255.1, U1.Y37
SVB_PWM2: R424.1, U1.AA36
SVB_PWM3: R256.1, U1.AA37
SYS_RSTN: J_CORE.86, U1.AN11
SYS_RSTN_OUT_WDG_RSTN: J_CORE.87, R437.2, U1.AR11
TEMP_ALERT: J_CAM.52, U1.D35
TEST_MODE: R226.1, U1.AP10
TP_I2C10_SCL: R28.2, U1.K34
TP_I2C10_SDA: R36.2, U1.L35
UART0_RXD_1V8: J_CORE.89, U1.AA35
UART0_TXD_1V8: J_CORE.88, U1.AB35
UPDATE_MODE_N: R467.2, U1.AC35
VDDIO_DDR0_CK: C261.1, LB41.2, U1.K11
VDDIO_DDR1_CK: C276.1, LB40.2, U1.L10
VDD_1V8: R250.2, U2.F1, U2.F12, U2.G4, U2.G9, U2.T4, U2.T9, U2.U1, U2.U12, U3.F1, U3.F12, U3.G4, U3.G9, U3.T4, U3.T9, U3.U1, U3.U12
WIFI_HOST_WAKE_TO_SOC: J_CORE.100, U1.A33
WIFI_PDN_FROM_SOC: J_CORE.99, U1.E37
WIFI_SDIO_CLK: J_CORE.69, U1.C37
WIFI_SDIO_CMD: J_CORE.71, U1.B36
WIFI_SDIO_D0: J_CORE.73, U1.D36
WIFI_SDIO_D1: J_CORE.75, U1.D37
WIFI_SDIO_D2: J_CORE.77, U1.D34
WIFI_SDIO_D3: J_CORE.79, U1.C35
WIFI_SDIO_PWR_EN_FROM_SOC: J_CORE.23, U1.C36
XCE: J_CAM.38, U1.AR27
XCLR: J_CAM.40, U1.AR26
XHS: J_CAM.44, U1.AU26
XIN: C447.1, R145.1, U1.AF1, X4.1
XOUT_SOC: R47.1, R145.2, U1.AF2
XOUT_XTAL: C452.1, R47.2, X4.3
XVS: J_CAM.42, R118.2, R700.1, U1.AU25
